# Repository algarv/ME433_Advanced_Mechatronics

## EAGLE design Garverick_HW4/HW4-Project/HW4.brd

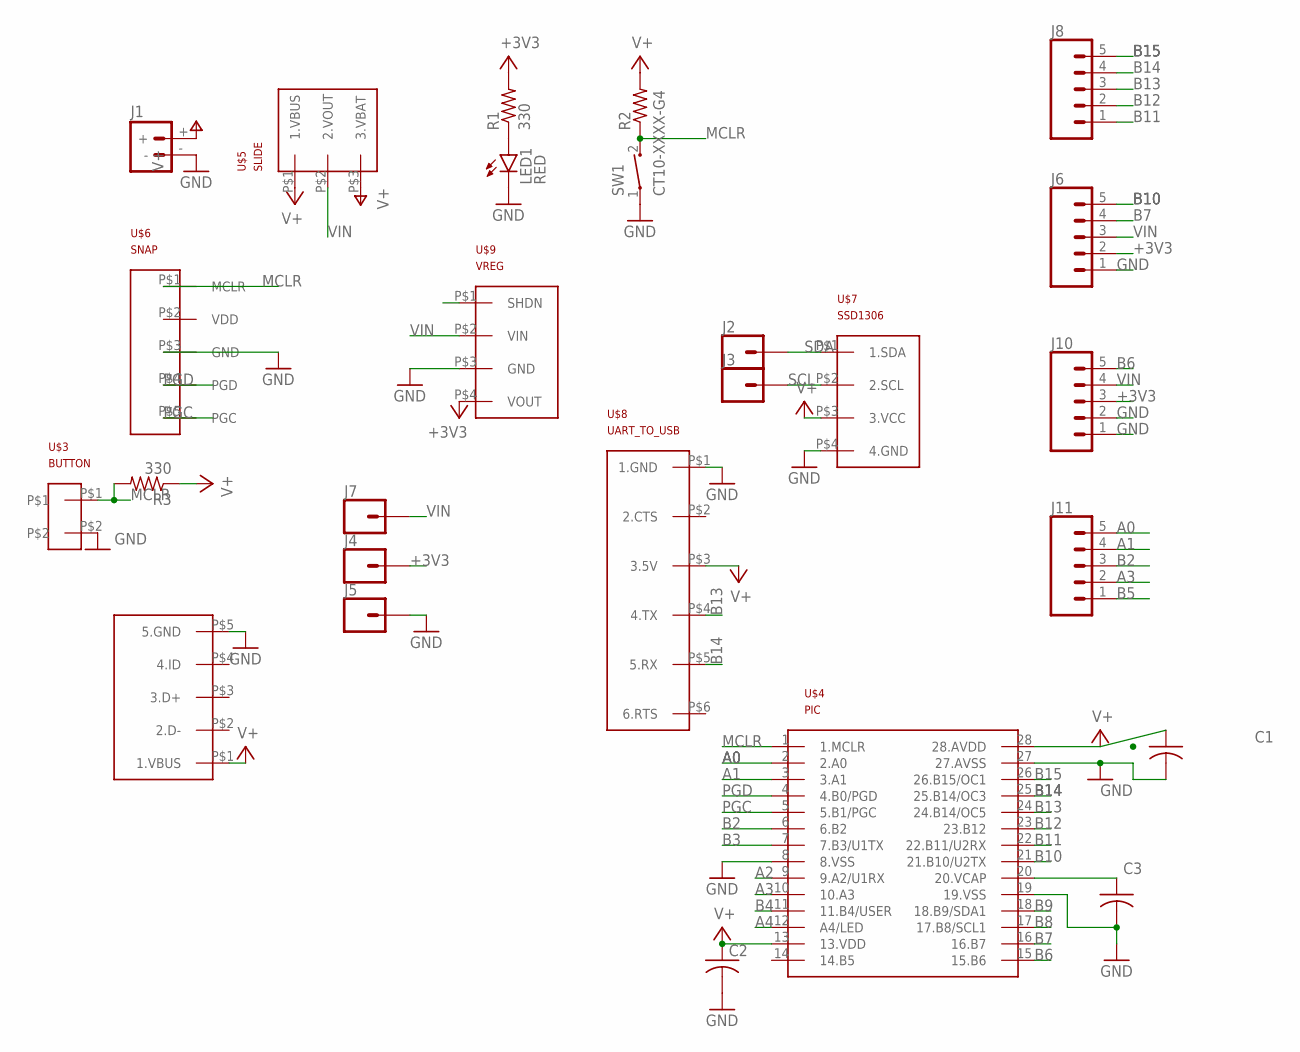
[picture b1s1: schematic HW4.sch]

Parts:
C1, C2, C3: C-US025-030X050; C025-030X050
J1: BATTERY_CONN_DEANS; DEANS
J2, J3: CONN_01; 1X01
J4, J5, J7: CONN_01PTH_2MM; 1X01_2MM
J6, J8, J10, J11: CONN_05; 1X05
LED1: RED; LED5MM
R1, R3: 330; 0204/7
R2: R-US_0309/10; 0309/10
SW1: CT10-XXXX-G4
U$3: BUTTON
U$4: PIC
U$5: SLIDE
U$6: SNAP
U$7: SSD1306
U$8: UART_TO_USB
U$9: VREG
U$10: MICROUSB

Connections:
+3V3: J4.1, J6.2, J10.3
A0: J11.5, U$4.2 (2.A0)
A1: J11.4, U$4.3 (3.A1)
A2: U$4.9 (9.A2/U1RX)
A3: J11.2, U$4.10 (10.A3)
A4: U$4.12 (A4/LED)
B2: J11.3, U$4.6 (6.B2)
B3: U$4.7 (7.B3/U1TX)
B4: U$4.11 (11.B4/USER)
B5: J11.1
B6: J10.5, U$4.15 (15.B6)
B7: J6.4, U$4.16 (16.B7)
B8: U$4.17 (17.B8/SCL1)
B9: U$4.18 (18.B9/SDA1)
B10: J6.5, U$4.21 (21.B10/U2TX)
B11: J8.1, U$4.22 (22.B11/U2RX)
B12: J8.2, U$4.23 (23.B12)
B13: J8.3, U$4.24 (24.B14/OC5), U$8.P$4 (4.TX)
B14: J8.4, U$4.25 (25.B14/OC3), U$8.P$5 (5.RX)
B15: J8.5, U$4.26 (26.B15/OC1)
GND: C1.2, C2.2, C3.2, J1.-, J5.1, J6.1, J10.1, J10.2, LED1.K (C), SW1.1, U$3.P$2, U$4.8 (8.VSS), U$4.19 (19.VSS), U$4.27 (27.AVSS), U$6.P$3 (GND), U$7.P$4 (4.GND), U$8.P$1 (1.GND), U$9.P$3 (GND), U$10.P$5 (5.GND)
MCLR: R2.1, R3.2, SW1.2, U$3.P$1, U$4.1 (1.MCLR), U$6.P$1 (MCLR)
unnamed: LED1.A, R1.1
unnamed: C3.1, U$4.20 (20.VCAP)
PGC: U$4.5 (5.B1/PGC), U$6.P$5 (PGC)
PGD: U$4.4 (4.B0/PGD), U$6.P$4 (PGD)
SCL: J3.1, U$7.P$2 (2.SCL)
SDA: J2.1, U$7.P$1 (1.SDA)
V+: C1.1, C2.1, J1.+, R1.2, R2.2, R3.1, U$4.13 (13.VDD), U$4.28 (28.AVDD), U$5.P$1 (1.VBUS), U$5.P$3 (3.VBAT), U$7.P$3 (3.VCC), U$8.P$3 (3.5V), U$9.P$4 (VOUT), U$10.P$1 (1.VBUS)
VIN: J6.3, J7.1, J10.4, U$5.P$2 (2.VOUT), U$9.P$2 (VIN)

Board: 2 copper layers, 28 parts (0 on the bottom side), 23 nets, no tracks yet.

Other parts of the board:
U$1, U$2: SNAP

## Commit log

2022-03-31 Uploading HW2
2022-04-01 Adding circuit images HW2
2022-04-05 Adding Homework 3
2022-04-05 Revert "Reverting Edits to Homework 2"
    This reverts commit 440b79c366b03321bc7fb8b62d82e85a5a71d8b7.
2022-04-05 Renaming project to HW3
2022-04-05 Apparently renaming was a bad idea
2022-04-05 Fixed Homework 3 upload
2022-04-05 Adding serial screen shot
2022-04-14 Uploading HW4 project files
2022-04-14 Uploading schematic picture
2022-04-14 Switching HW2 and HW3
2022-04-22 Uploading HW 5
2022-04-29 Uploading HW6
2022-05-07 Finished HW9
2022-05-07 Finished HW7
2022-05-09 Finished HW8
2022-05-11 Finished HW10
2022-05-20 Finished HW11

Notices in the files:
parts and their libraries:
SparkFun-Connectors: Licensing: Creative Commons ShareAlike 4.0 International - https://creativecommons.org/licenses/by-sa/4.0
